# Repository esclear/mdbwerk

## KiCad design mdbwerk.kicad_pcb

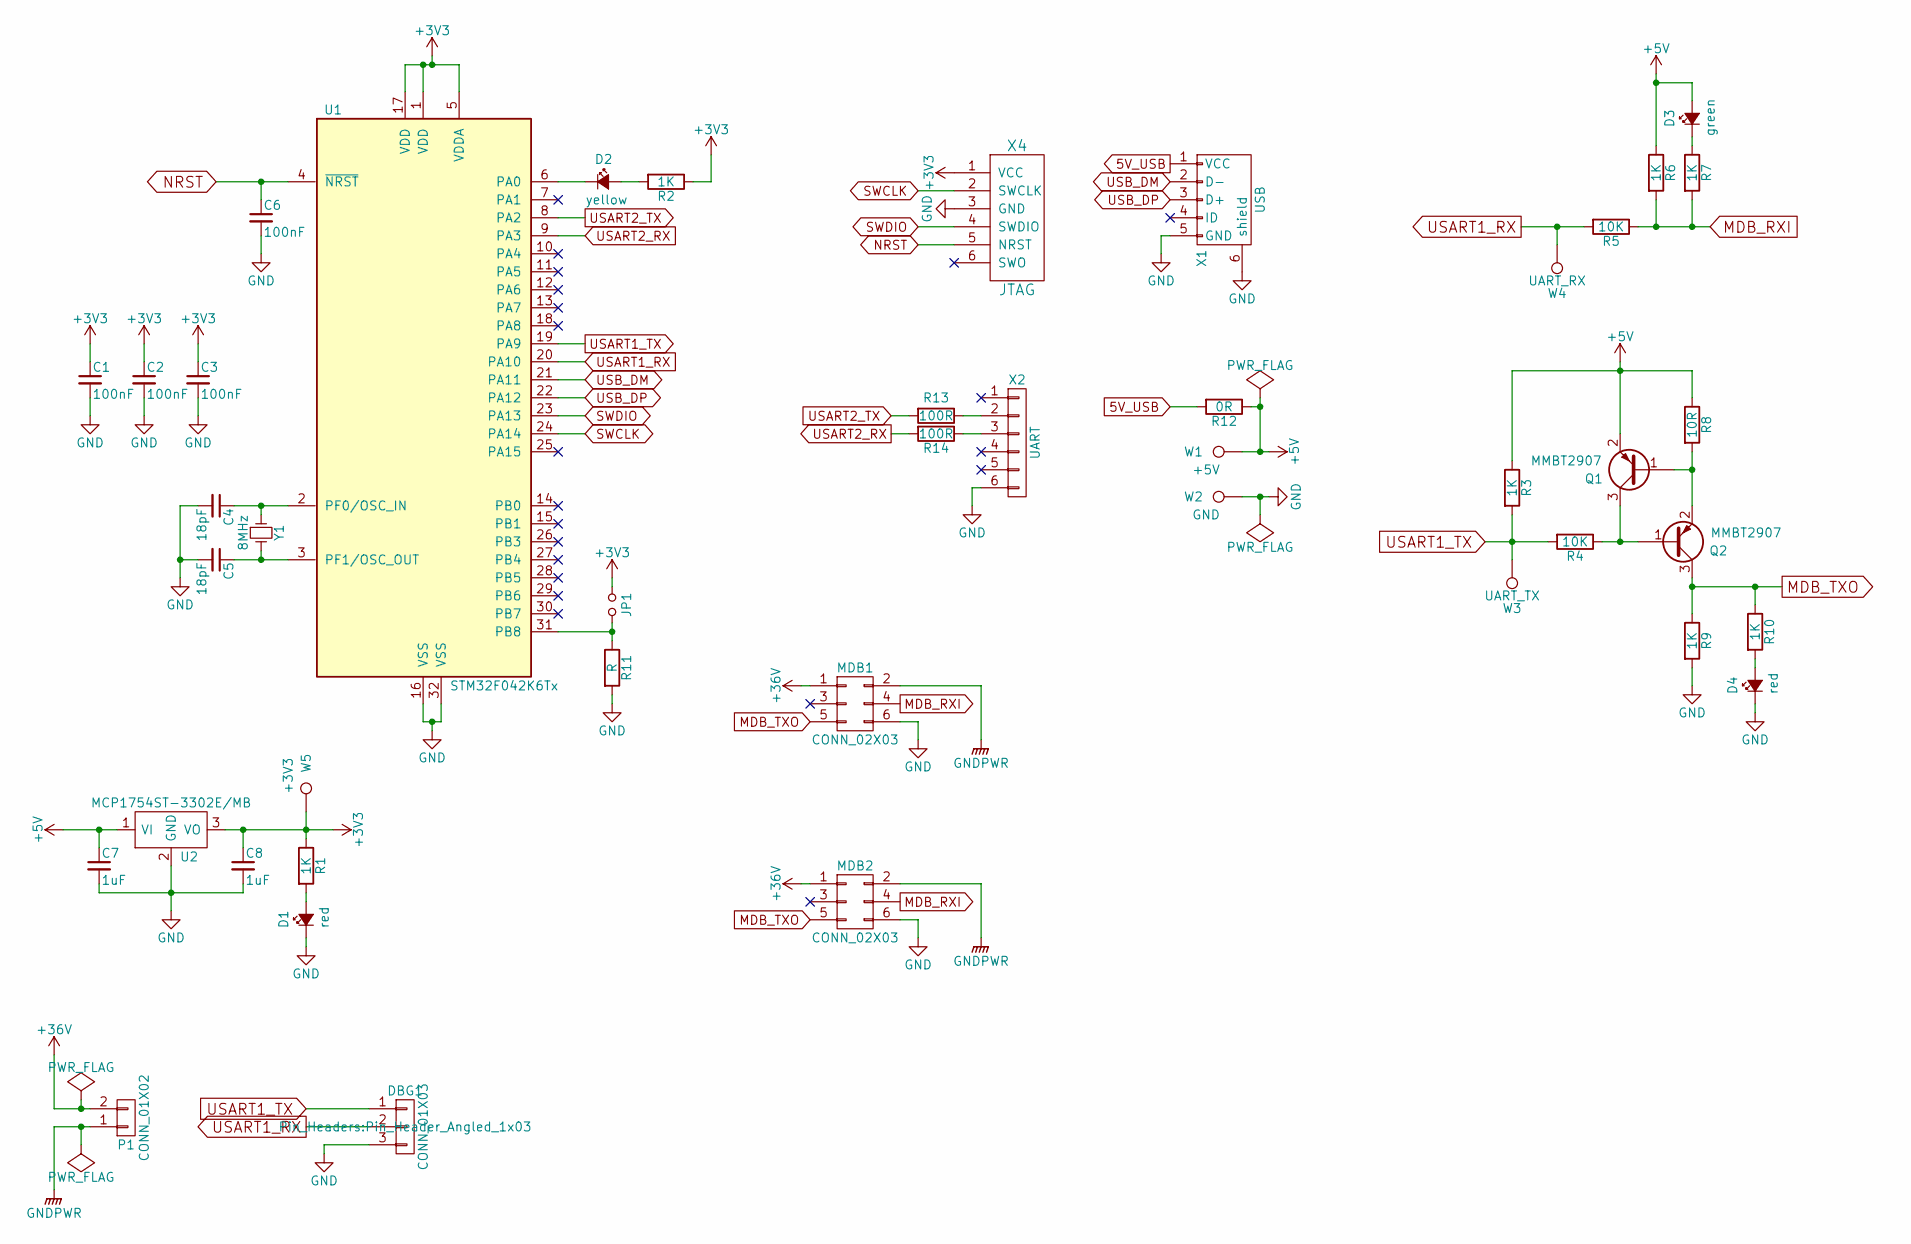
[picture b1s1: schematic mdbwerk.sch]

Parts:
C1, C2, C3, C6: 100nF; C_0603
C4, C5: 18pF; C_0603
C7, C8: 1uF; C_0603
D1, D4: red; LED_0603
D2: yellow; LED_0603
D3: green; LED_0603
DBG1: CONN_01X03; Pin_Header_Angled_1x03
JP1: Jumper_NO_Small; R_1206
MDB1, MDB2: CONN_02X03; Molex_MiniFit-JR-5569-06A2_2x03x4.20mm_Angled
P1: CONN_01X02; TE-282836-2
Q1, Q2: MMBT2907; SOT-23
R1, R2, R3, R6, R7, R9, R10: 1K; R_0603
R4, R5: 10K; R_0603
R8: 10R; R_0603
R11: R; R_0603
R12: 0R; R_0603
R13, R14: 100R; R_0603
U1: STM32F042K6Tx; LQFP-32_7x7mm_Pitch0.8mm
U2: MCP1754ST-3302E/MB; SOT89-3_Housing
W1: +5V; Measurement_Point_Round-SMD-Pad_Big
W2: GND; Measurement_Point_Round-SMD-Pad_Big
W3: UART_TX; Measurement_Point_Round-SMD-Pad_Small
W4: UART_RX; Measurement_Point_Round-SMD-Pad_Small
W5: +3V3; Measurement_Point_Round-SMD-Pad_Big
X1: USB; Molex-Micro-USB-B-Middle-Mount
X2: UART; Pin_Header_Straight_1x06
X4: JTAG; TC2030-NL
Y1: 8MHz; ABM3

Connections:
5V_USB: R12.2, X1.1 (VCC)
+3V3: C1.1, C2.1, C3.1, C8.1, JP1.1, R1.1, R2.1, U1.1 (VDD), U1.5 (VDDA), U1.17 (VDD), U2.3 (VO), W5.1, X4.1 (VCC)
+5V: C7.1, D3.2 (A), Q1.2 (E), R3.1, R6.1, R8.1, R12.1, U2.1 (VI), W1.1
+36V: MDB1.1, MDB2.1, P1.2
GND: C1.2, C2.2, C3.2, C4.2, C5.2, C6.2, C7.2, C8.2, D1.1 (K), D4.1 (K), DBG1.3, MDB1.6, MDB2.6, R9.2, R11.2, U1.16 (VSS), U1.32 (VSS), U2.2 (GND), W2.1, X1.5 (GND), X1.6 (shield), X2.6, X4.3 (GND)
GNDPWR: MDB1.2, MDB2.2, P1.1
MDB_RXI: MDB1.4, MDB2.4, R5.1, R6.2, R7.2
MDB_TXO: MDB1.5, MDB2.5, Q2.3 (C), R9.1, R10.1
NRST: C6.1, U1.4 (~NRST), X4.5 (NRST)
unnamed: C4.1, U1.2 (PF0/OSC_IN), Y1.1
unnamed: C5.1, U1.3 (PF1/OSC_OUT), Y1.2
unnamed: D1.2 (A), R1.2
unnamed: D2.1 (K), U1.6 (PA0)
unnamed: D2.2 (A), R2.2
unnamed: D3.1 (K), R7.1
unnamed: D4.2 (A), R10.2
unnamed: JP1.2, R11.1, U1.31 (PB8)
unnamed: Q1.1 (B), Q2.2 (E), R8.2
unnamed: Q1.3 (C), Q2.1 (B), R4.1
unnamed: R13.1, X2.2
unnamed: R14.1, X2.3
SWCLK: U1.24 (PA14), X4.2 (SWCLK)
SWDIO: U1.23 (PA13), X4.4 (SWDIO)
USART1_RX: DBG1.2, R5.2, U1.20 (PA10), W4.1
USART1_TX: DBG1.1, R3.2, R4.2, U1.19 (PA9), W3.1
USART2_RX: R14.2, U1.9 (PA3)
USART2_TX: R13.2, U1.8 (PA2)
USB_DM: U1.21 (PA11), X1.2 (D-)
USB_DP: U1.22 (PA12), X1.3 (D+)

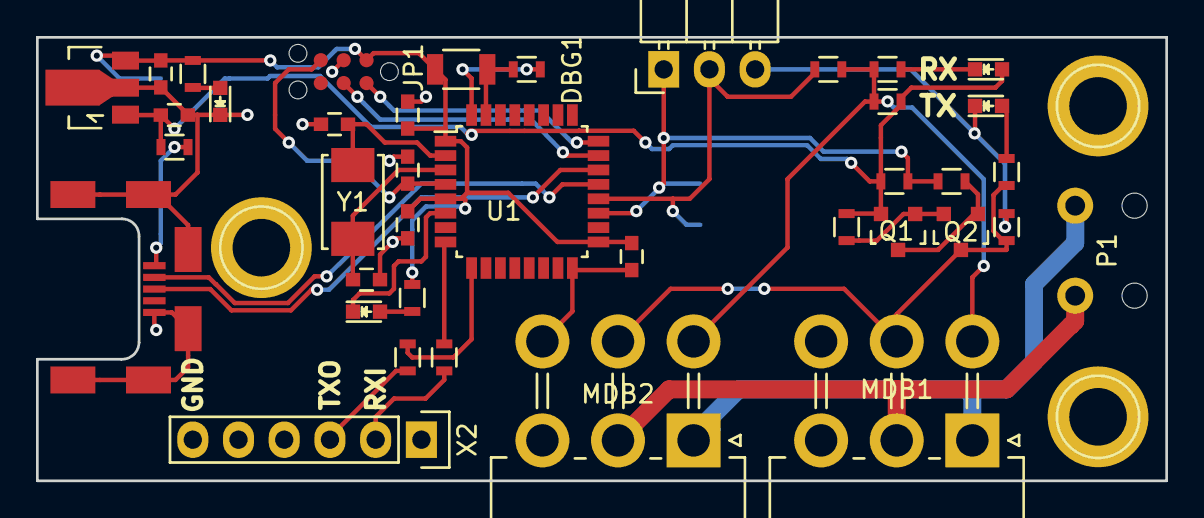
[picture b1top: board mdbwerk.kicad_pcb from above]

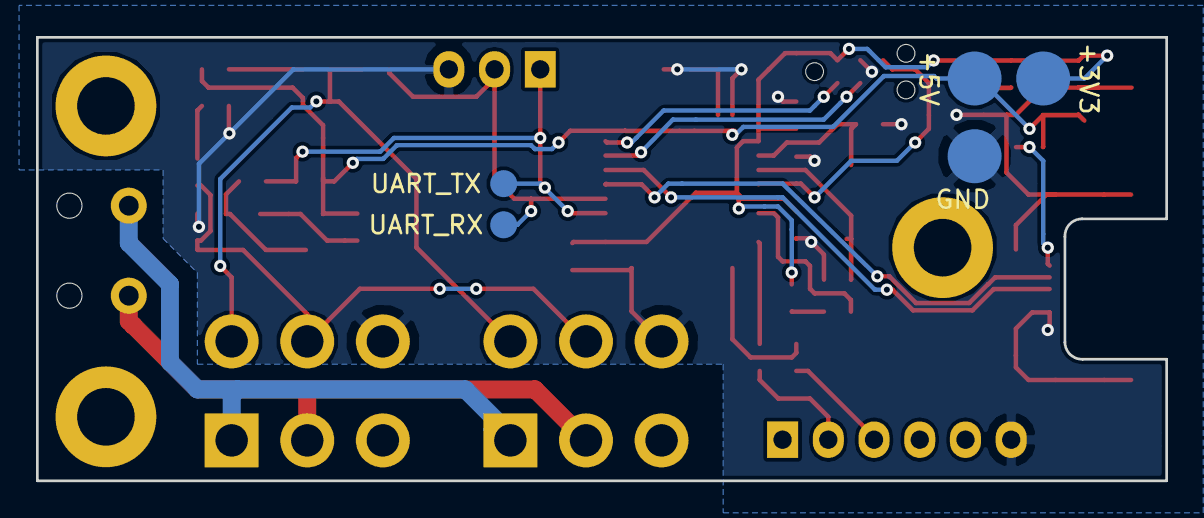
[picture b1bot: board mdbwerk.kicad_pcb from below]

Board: 2 copper layers, 62.7 x 24.6 mm, 47 parts (5 on the bottom side), 29 nets.

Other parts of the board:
M1, M1#2, M1#3: 1pin

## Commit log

2016-08-16 Bulkier board that supports multiple devices
2016-08-16 Now with mounting holes!
